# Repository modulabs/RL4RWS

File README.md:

# 모두의 연구소 : RL4RWS (시즌3)

## 연구실 소개
RL4RWS 랩은 **임베디드와 강화학습을 접목**하여 실제 환경에서 작동하는 다양한 모델을 직접 구현해 보는것을 목표로 합니다. 
 
## 연구실 목표
임베디드 분야와 강화학습 분야로 나누어서 세미나 진행 합니다.  

시즌 3의 진행 목표는 `NVIDIA Jetson TX2 기반 자율주행 RC카`를 제작하는 것입니다. 이를 위해 강화학습 이론과 RC카 제작 및 제어에 필요한 이론들을 학습할 계획입니다.   

### 강화학습 및 딥러닝 세미나 
#### 강화학습

김성훈 교수 강좌를 기반으로 강화학습 기초 세미나를 진행하였습니다.  
[모두를 위한 RL 강좌 유투브 채널](https://www.youtube.com/watch?v=dZ4vw6v3LcA&list=PLlMkM4tgfjnKsCWav-Z2F-MMFRx-2gMGG)  
[모두를 위한 머신러닝/딥러닝 강의 페이지](https://hunkim.github.io/ml/)  

#### 딥러닝
RL4RWS 연구원들의 실제 구현 사례를 바탕으로 세미나를 진행하였습니다.  
1. 조아라 연구원 : Udacity Self-Driving Car Nano-Degree 프로젝트 경험 공유  
    - [Traffic Sign Classifier](https://github.com/ahracho/CarND-Traffic-Sign-Classifier-Project)
    - [자율주행 시뮬레이션](https://github.com/ahracho/CarND-Behavioral-Cloning-P3) 
    - [Object Detection](https://github.com/ahracho/CarND-Vehicle-Detection)

2. 황보찬 연구원 : Yolo v3를 이용한 얼굴검출 및 표정인식  
3. 김민규 연구원 : GoogleNet 이용한 시각장애인용 길안내 (물체인식 프로젝트)   

### 임베디드 플랫폼 구축 관련 세미나
**1. NVIDIA Jetson TX2 (조진제 연구원)**   
    - Jetpack 설치 안내  
    - Jetson-inference 구조에 대한 설명과 데모  
    - Deep Learning deployment with tensorRT  

**2. TF-Slim 분석** : 저수준의 텐서플로우 API를 간편하게 사용할 수 있는 고수준 경량 API  
    **<참고자료>**  
    - [TF-slim 시작하기](https://www.popit.kr/tf-slim-%EC%8B%9C%EC%9E%91%ED%95%98%EA%B8%B0/)  
    - [TF-slim 분석 자료](./tf_slim)  
    - [TF-slim 예제 소스코드 (1) MNIST](https://github.com/socurites/tf-slim-tutorial)  
    - [TF-slim 예제 소스코드 (2) Dog Breed Classifier](https://github.com/socurites/dog-breed-classification.tf)  

**3. Tensorflow 활용한 YOLO**  
   **<참고자료>**  
    - [소스코드](./tf_yolo)  

### 센서 및 제어이론 관련 세미나
1. ROS 간단한 예제 설명 및 SLAM (이승진 연구원)  
2. PID 개론 (유지원 연구원)  
3. 최신 카메라 센서 동향 (장해강 연구원)  

### 참고자료
- [YOLOv2 On Jetson TX2](https://jkjung-avt.github.io/yolov2/)
- [YOLOv3 On Jetson TX2](https://jkjung-avt.github.io/yolov3/)
- [Jetson Race Car 예제](https://www.jetsonhacks.com/2016/01/26/jetson-racecar-part-3-esc-motor-control/)
- [버클리 강화학습 기반 RC카 github](https://github.com/gkahn13/gcg)  
- [TF-Slim](https://www.popit.kr/tf-slim-%EC%8B%9C%EC%9E%91%ED%95%98%EA%B8%B0/)
- [NVIDIA Jetson TX2 - JetPack](https://developer.nvidia.com/embedded/jetpack)  
- [모두를 위한 머신러닝/딥러닝](https://hunkim.github.io/ml/)

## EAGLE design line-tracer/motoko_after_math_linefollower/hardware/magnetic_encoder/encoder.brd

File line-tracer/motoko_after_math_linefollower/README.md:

# motoko_after_math_linefollower

본 프로젝트의 소스코드는 https://github.com/michalnand/motoko_after_math_linefollower 를 기반으로  
RL4RWS Lab에서 실습 상황에 맞게 수정하였습니다.

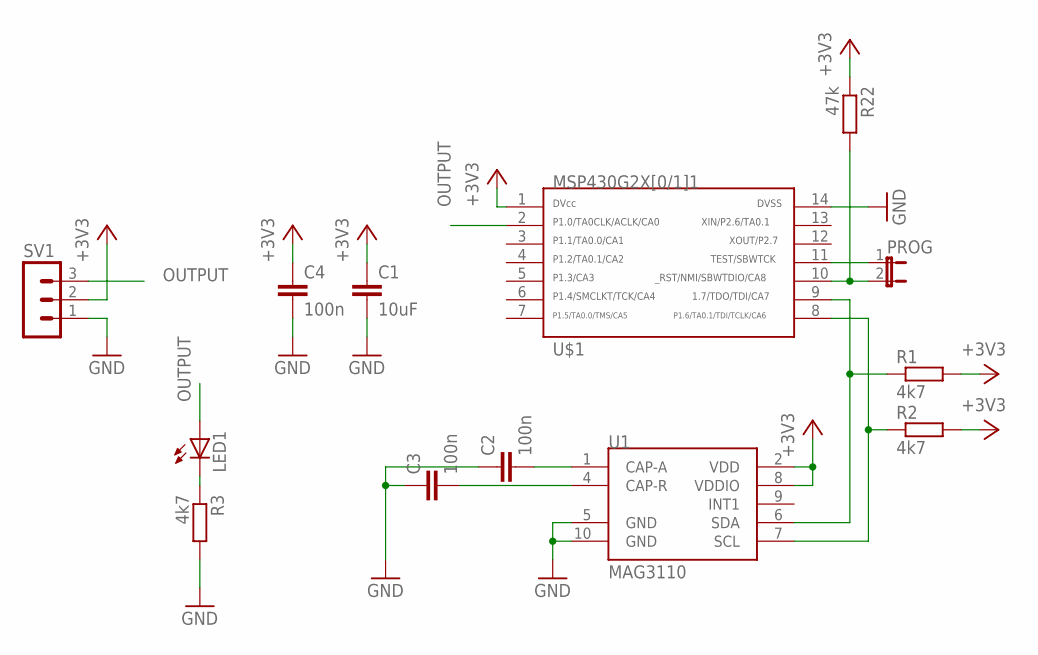
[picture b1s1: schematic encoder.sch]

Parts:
C1: 10uF; C0805
C2, C3, C4: 100n; C0805
LED1: LEDSML1206; SML1206
PROG: JP1E; JP1
R1, R2, R3: 4k7; M0805
R22: 47k; M0805
SV1: MA03-1
U1: MAG3110; DFN-10
U$1: G2X[0/1]1---PW14; PW14

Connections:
+3V3: C1.1, C4.1, R1.2, R2.2, R22.1, SV1.2, U1.2 (VDD), U1.8 (VDDIO), U$1.1
GND: C1.2, C2.1, C3.1, C4.2, R3.2, SV1.1, U1.5 (GND), U1.10 (GND), U$1.14
unnamed: PROG.1, U$1.11
unnamed: PROG.2, R22.2, U$1.10
unnamed: R1.1, U1.6 (SDA), U$1.9
unnamed: R2.1, U1.7 (SCL), U$1.8
unnamed: C3.2, U1.4 (CAP-R)
unnamed: C2.2, U1.1 (CAP-A)
unnamed: LED1.C, R3.1
OUTPUT: LED1.A, SV1.3, U$1.2

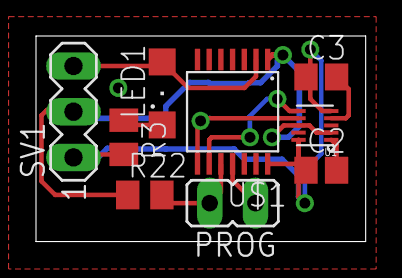
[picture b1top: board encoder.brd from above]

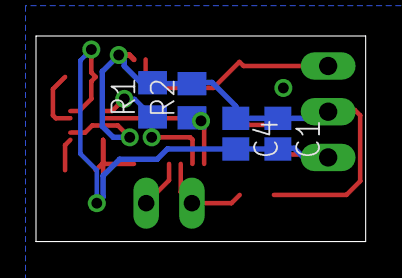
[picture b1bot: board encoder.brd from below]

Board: 2 copper layers, 18.3 x 11.4 mm, 13 parts (4 on the bottom side), 10 nets.

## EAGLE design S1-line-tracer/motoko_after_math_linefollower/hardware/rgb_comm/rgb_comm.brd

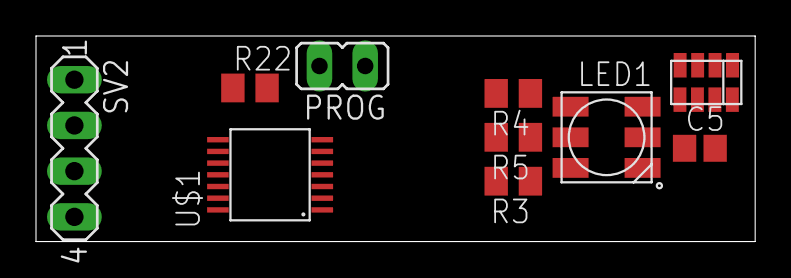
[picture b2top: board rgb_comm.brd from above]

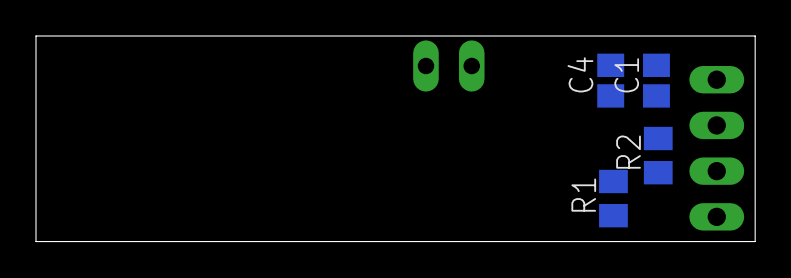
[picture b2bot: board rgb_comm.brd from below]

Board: 2 copper layers, 40.0 x 11.4 mm, 14 parts (4 on the bottom side), 13 nets, no tracks yet.

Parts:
C1, C5: 10uF; C0805
C4: 100n; C0805
LED1: ADAFRUIT_RGBLED5050
PROG: JP1
R1, R2: 4k7; M0805
R3, R4, R5: 330; M0805
R22: 47k; M0805
SV2: MA04-1
U$1: G2X[0/1]1---PW14; PW14
U$2: APDS9950

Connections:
+3V3: C1.1, C4.1, C5.1, R1.2, R2.2, R22.1, SV2.2, U$1.1, U$2.P$5, U$2.P$8
GND: C1.2, C4.2, C5.2, LED1.4, LED1.5, LED1.6, SV2.1, U$1.14, U$2.P$6
unnamed: PROG.1, U$1.11
unnamed: PROG.2, R22.2, U$1.10
unnamed: LED1.3, R3.1
unnamed: LED1.1, R4.1
unnamed: U$2.P$3, U$2.P$4
unnamed: LED1.2, R5.1
unnamed: R3.2, U$1.2
unnamed: R4.2, U$1.3
unnamed: R5.2, U$1.4
SCL: R2.1, SV2.3, U$1.8, U$2.P$7
SDA: R1.1, SV2.4, U$1.9, U$2.P$1

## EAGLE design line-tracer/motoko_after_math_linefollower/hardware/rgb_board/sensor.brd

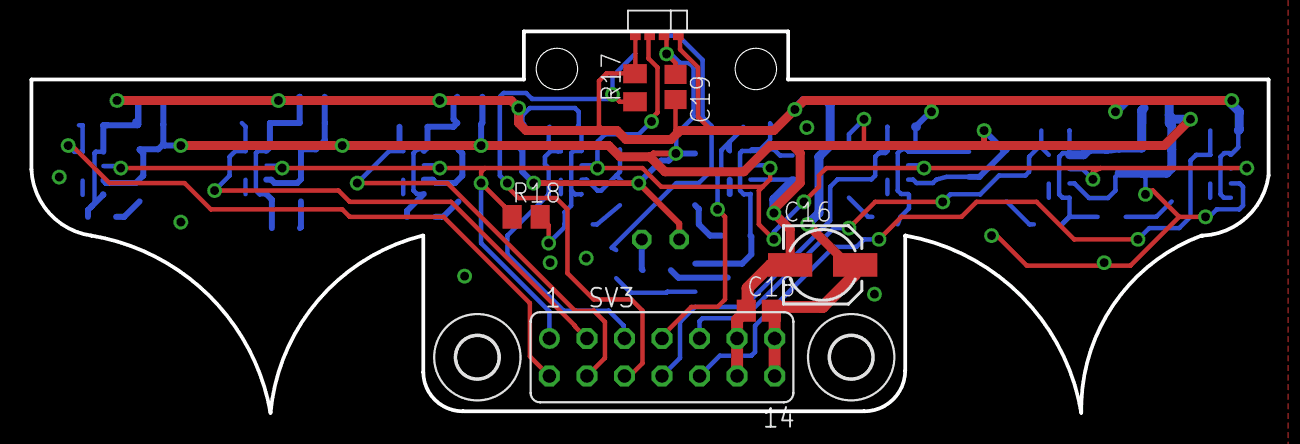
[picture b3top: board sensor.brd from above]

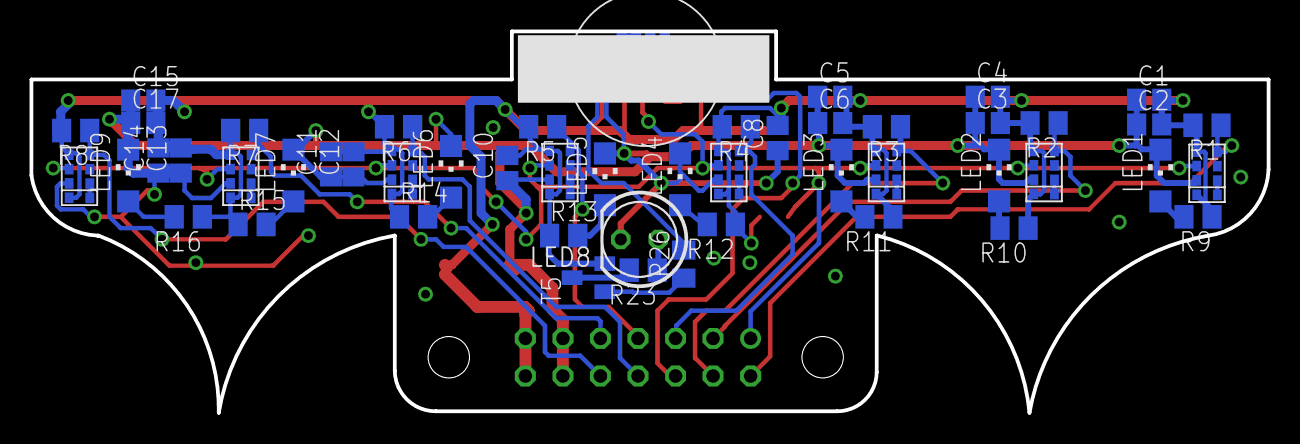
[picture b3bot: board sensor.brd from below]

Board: 2 copper layers, 83.7 x 25.8 mm, 60 parts (51 on the bottom side), 32 nets.

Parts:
C1, C3, C5, C11, C13, C15, C18: 10uF; C0805
C2, C4, C6, C8, C10, C12, C14, C17, C19: 100n; C0805
C16: 22uF; 153CLV-0505
H3, H4: MOUNT-HOLE2.8; 2,8
LED1, LED2, LED3, LED4, LED5, LED6, LED7, LED9: CHIPLED_1206
LED8: LED5MM
R1, R2, R3, R4, R5, R6, R7, R8, R17, R18: 4k7; M0805
R9, R10, R11, R12, R13, R14, R15, R16, R26: 330; M0805
R23: 22; M0805
SV3: FE07-2
T5: SOT23-BEC
U$1, U$4, U$5, U$6, U$7, U$8, U$9, U$10: APDS9950
U$2: APDS9950_EDGE
U$3: BALL_3/8

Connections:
+3V3: C1.2, C2.2, C3.2, C4.2, C5.2, C6.2, C8.2, C10.2, C11.2, C12.2, C13.2, C14.2, C15.2, C16.+, C17.2, C18.2, C19.2, R1.2, R2.2, R3.2, R4.2, R5.2, R6.2, R7.2, R8.2, R9.1, R10.1, R11.1, R12.1, R13.1, R14.1, R15.1, R16.1, R17.2, R18.2, SV3.13, SV3.14, T5.E, U$1.P$5, U$1.P$8, U$2.P$5, U$2.P$8, U$4.P$5, U$4.P$8, U$5.P$5, U$5.P$8, U$6.P$5, U$6.P$8, U$7.P$5, U$7.P$8, U$8.P$5, U$8.P$8, U$9.P$5, U$9.P$8, U$10.P$5, U$10.P$8
ADC0_: R8.1, SV3.10, U$10.P$1
ADC1_: R7.1, SV3.9, U$9.P$1
ADC2_: R6.1, SV3.8, U$8.P$1
ADC3_: R5.1, SV3.7, U$7.P$1
ADC4_: R4.1, SV3.5, U$6.P$1
ADC5_: R3.1, SV3.4, U$5.P$1
ADC6_: R2.1, SV3.3, U$4.P$1
ADC7_: R1.1, SV3.2, U$1.P$1
ADC8_: R17.1, SV3.6, U$2.P$1
GND: C1.1, C2.1, C3.1, C4.1, C5.1, C6.1, C8.1, C10.1, C11.1, C12.1, C13.1, C14.1, C15.1, C16.-, C17.1, C18.1, C19.1, LED1.C, LED2.C, LED3.C, LED4.C, LED5.C, LED6.C, LED7.C, LED8.K, LED9.C, SV3.11, SV3.12, U$1.P$6, U$2.P$6, U$4.P$6, U$5.P$6, U$6.P$6, U$7.P$6, U$8.P$6, U$9.P$6, U$10.P$6
unnamed: R23.2, T5.C
unnamed: U$4.P$3, U$4.P$4
unnamed: LED1.A, R9.2
unnamed: U$1.P$3, U$1.P$4
unnamed: LED2.A, R10.2
unnamed: LED3.A, R11.2
unnamed: LED4.A, R12.2
unnamed: LED5.A, R13.2
unnamed: U$5.P$3, U$5.P$4
unnamed: LED6.A, R14.2
unnamed: LED7.A, R15.2
unnamed: U$6.P$3, U$6.P$4
unnamed: LED9.A, R16.2
unnamed: R26.2, U$2.P$3, U$2.P$4
unnamed: U$7.P$3, U$7.P$4
unnamed: U$8.P$3, U$8.P$4
unnamed: U$9.P$3, U$9.P$4
unnamed: LED8.A, R23.1
unnamed: U$10.P$3, U$10.P$4
unnamed: R26.1, T5.B
SCL: R18.1, SV3.1, U$1.P$7, U$2.P$7, U$4.P$7, U$5.P$7, U$6.P$7, U$7.P$7, U$8.P$7, U$9.P$7, U$10.P$7

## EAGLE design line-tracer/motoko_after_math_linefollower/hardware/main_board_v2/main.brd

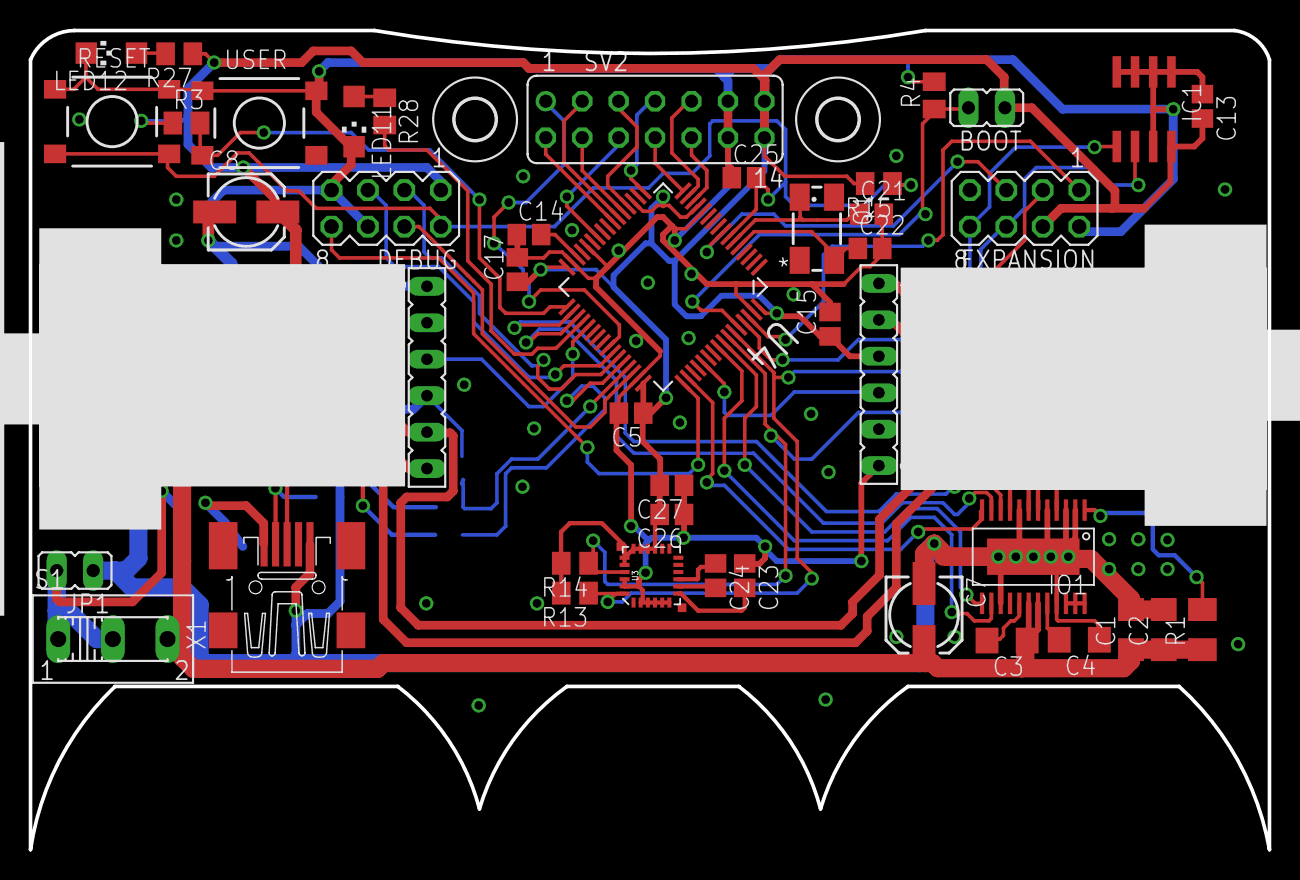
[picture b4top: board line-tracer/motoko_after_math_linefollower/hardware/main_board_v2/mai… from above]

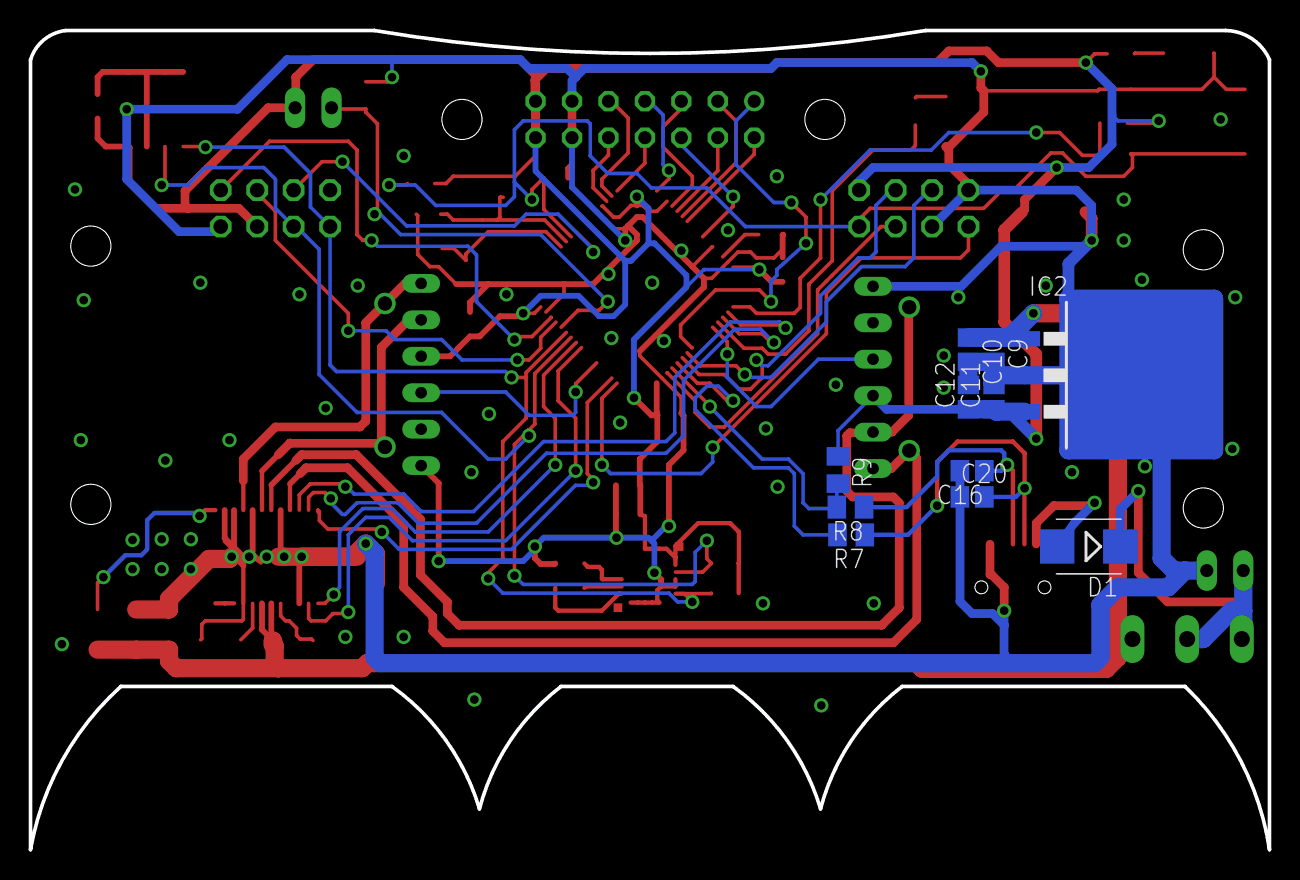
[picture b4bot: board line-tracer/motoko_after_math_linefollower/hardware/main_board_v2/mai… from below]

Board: 2 copper layers, 86.4 x 57.1 mm, 59 parts (11 on the bottom side), 55 nets.

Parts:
BOOT: JP1
C1: 100n; C1206
C2: 10uF; C1206
C3: 10n; C1206
C4: 1uF; C1206
C5, C9, C11, C13, C15, C17, C25, C26: 100n; C0805
C7, C8: 22uF; 153CLV-0505
C10, C12, C27: 10uF; C0805
C14, C23: 4.7uF; C0805
C16, C20: 22p; C0805
C21, C22: 18p; C0805
C24: 220n; C0805
D1: SMB
DEBUG: MA04-2
EXPANSION: MA04-2
H1, H2: MOUNT-HOLE2.8; 2,8
IC1: 24AA32ASN; SO-08
IC2: LM2937; TO263-3
IO1: DRV8834; DRV8834_PCK
JP1: 2 CellLi-Pol; JP1
LED11: CHIPLED_1206
LED12: poweron; CHIPLED_1206
Q1: 8MHz; CTS406
R1: 47k; M1206
R3, R4, R15: 47k; M0805
R7, R8: 22; M0805
R9: 1k5; M0805
R13, R14: 4k7; M0805
R27, R28: 330; M0805
RESET: DTSM-6
S1: 255SB
SV1, SV3: FE06
SV2: FE07-2
U3: LSM9DS0; LGA-24
U4: STM32F303RCT6; QFP50P1200X1200X160-64N
U$1, U$2: MICRO_METAL_GEAR_MOTOR
USER: DTSM-6
X1: MINI-USB-32005-201; 32005-201

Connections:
+3V3: BOOT.1, C5.1, C8.+, C11.1, C12.1, C13.2, C15.1, C17.1, C26.2, C27.2, DEBUG.1, EXPANSION.4, IC1.8, IC2.3, R3.1, R9.1, R13.2, R14.2, R15.2, R27.1, SV1.3, SV2.13, SV2.14, SV3.3, U3.15, U3.16, U3.17, U3.18, U3.19, U3.20, U4.13, U4.19, U4.32, U4.48, U4.64
ADC0: SV2.10, U4.14
ADC1: SV2.9, U4.15
ADC2: SV2.8, U4.16
ADC3: SV2.7, U4.17
ADC4: SV2.5, U4.20
ADC5: SV2.4, U4.21
ADC6: SV2.3, U4.22
ADC7: SV2.2, U4.23
ADC8: SV2.6, U4.26
AENBL: IO1.10, U4.34
APHASE: IO1.13, U4.57
BATT: D1.C, JP1.2, S1.1, S1.2
BENBL: IO1.11, U4.35
BOOT: BOOT.2, R4.1, U4.60
BPHASE: IO1.12, U4.50
CAM_AO: EXPANSION.5, U4.8
CAM_CLK: EXPANSION.3, U4.61
CAM_SI: EXPANSION.1, U4.62
GND: C1.2, C2.2, C4.1, C5.2, C7.-, C8.-, C9.2, C10.2, C11.2, C12.2, C13.1, C14.1, C15.2, C16.2, C17.2, C20.1, C21.2, C22.2, C23.1, C25.1, C26.1, C27.1, DEBUG.6, DEBUG.7, EXPANSION.2, IC1.1, IC1.2, IC1.3, IC1.4, IC1.7, IC2.2, IO1.2, IO1.3, IO1.5, IO1.8, IO1.15, IO1.21, IO1.PAD, JP1.1, LED11.C, LED12.C, R4.2, RESET.1, RESET.2, SV1.6, SV2.11, SV2.12, SV3.6, U3.2, U3.3, U3.4, U3.5, U3.6, U3.22, U3.23, U4.12, U4.28, U4.31, U4.47, U4.63, USER.1, USER.2, X1.5
IR_CONTROLL: SV2.1, U4.41
LED_1: R28.2, U4.36
LEFT_ENC: SV1.4, U4.37
M1: IO1.14, U4.56
unnamed: IO1.4, SV3.1, U$1.P$1
unnamed: IO1.6, SV3.2, U$1.P$2
unnamed: IO1.9, SV1.1, U$2.P$1
unnamed: IO1.7, SV1.2, U$2.P$2
unnamed: C3.2, IO1.17
unnamed: C23.2, U3.7
unnamed: C24.2, U3.8
unnamed: IO1.22, IO1.23, IO1.24
unnamed: IO1.1, R1.2
unnamed: C24.1, U3.9
unnamed: C14.2, U4.30
unnamed: C4.2, IO1.20
unnamed: LED12.A, R27.2
unnamed: LED11.A, R28.1
unnamed: C20.2, R7.1, X1.2
unnamed: C16.1, R8.1, X1.3
unnamed: D1.A, X1.1
OSCIN: C22.1, Q1.3, U4.5
OSCOUT: C21.1, Q1.1, U4.6
RESET: C25.2, DEBUG.2, R15.1, RESET.3, RESET.4, U4.7
RIGHT_ENC: SV3.4, U4.53
SCL: EXPANSION.6, IC1.6, R14.1, U3.21, U4.58
SDA: EXPANSION.8, IC1.5, R13.1, U3.24, U4.59
SWCLK: DEBUG.8, U4.49
SWDIO: DEBUG.4, U4.46
UART_RX: DEBUG.3, U4.43
UART_TX: DEBUG.5, U4.42
USBDM: R7.2, U4.44
USBDP: R8.2, R9.2, U4.45
USER_KEY_1: R3.2, U4.33, USER.3
VCC: C1.1, C2.1, C3.1, C7.+, C9.1, C10.1, IC2.1, IO1.18, IO1.19, R1.1, S1.3

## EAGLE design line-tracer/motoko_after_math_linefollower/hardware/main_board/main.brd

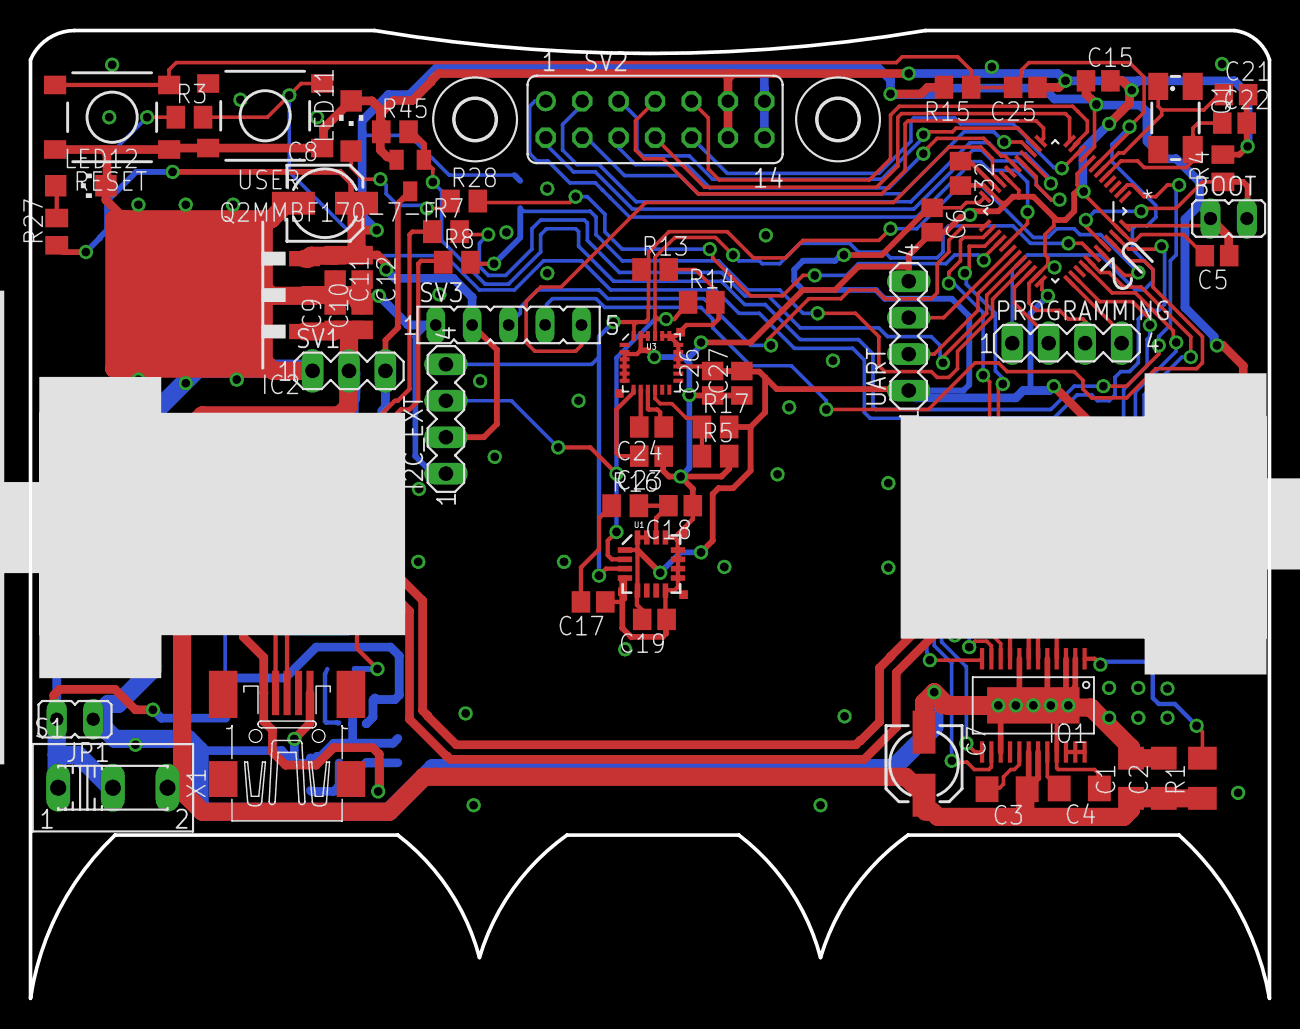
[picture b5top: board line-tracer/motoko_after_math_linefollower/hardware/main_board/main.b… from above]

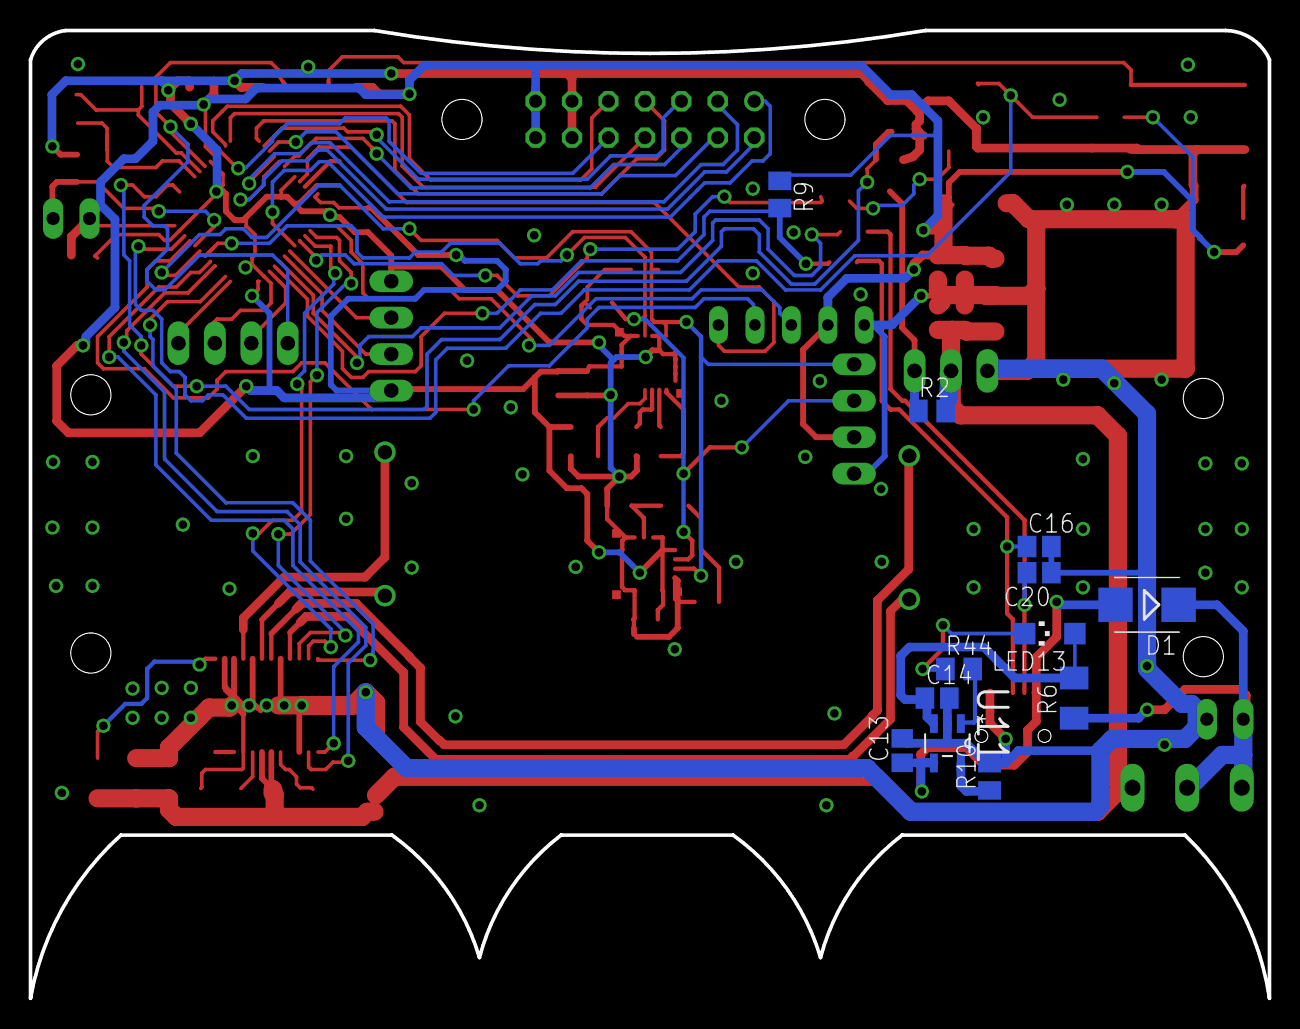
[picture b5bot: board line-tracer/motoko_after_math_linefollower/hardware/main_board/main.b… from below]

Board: 2 copper layers, 86.4 x 67.5 mm, 75 parts (12 on the bottom side), 62 nets.

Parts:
BOOT: JP1
C1: 100n; C1206
C2: 10uF; C1206
C3: 10n; C1206
C4: 1uF; C1206
C5, C9, C11, C15, C19, C25, C26: 100n; C0805
C6, C10, C12, C13, C14, C27: 10uF; C0805
C7, C8: 22uF; 153CLV-0505
C16, C20: 22p; C0805
C17: 470n; C0805
C18: 10n; C0805
C21, C22: 18p; C0805
C23, C32: 4.7uF; C0805
C24: 220n; C0805
D1: SMB
H1, H2: MOUNT-HOLE2.8; 2,8
I2C_EXT: MA04-1
IC2: LM2937; TO263-3
IO1: DRV8834; DRV8834_PCK
JP1: 2 CellLi-Pol; JP1
LED11: CHIPLED_1206
LED12: poweron; CHIPLED_1206
LED13: charging; CHIPLED_1206
PROGRAMMING: MA04-1
Q1: 8MHz; CTS406
Q2MMBF170-7-F: BSS123; SOT23
R1: 47k; M1206
R2, R3, R4, R5, R15, R17, R45: 47k; M0805
R6: 0R USE ONLY FOR SINGLE CELL; M1206
R7, R8: 22; M0805
R9: 1k5; M0805
R10, R16: 10k; M0805
R13, R14: 4k7; M0805
R27, R28, R44: 330; M0805
RESET: DTSM-6
S1: 255SB
SV1: SERVO/PWM; MA03-1
SV2: FE07-2
SV3: TSL1401 CAMERA; FE05-1
U1: L3G4200D; LGA16-4X4
U2: STM32F103C6T6A; QFP50P900X900X160-48N
U3: LSM9DS0; LGA-24
U11: MCP73831T-2DCI/OT; SOT95P270X145-5N
U$1, U$2: MICRO_METAL_GEAR_MOTOR
UART: MA04-1
USER: DTSM-6
X1: MINI-USB-32005-201; 32005-201

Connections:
+3V3: BOOT.1, C5.1, C6.1, C8.+, C11.1, C12.1, C15.1, C19.2, C26.2, C27.2, I2C_EXT.2, IC2.3, R3.1, R9.1, R13.2, R14.2, R15.2, R17.2, R27.1, SV2.13, SV2.14, SV3.2, U1.1, U1.5, U1.15, U1.16, U2.9, U2.24, U2.36, U2.48, U3.15, U3.16, U3.17, U3.18, U3.19, U3.20, UART.1
ADC0: SV2.10, U2.10
ADC1: SV2.9, U2.11
ADC2: SV2.8, U2.12
ADC3: SV2.7, U2.13
ADC4: SV2.5, U2.14
ADC5: SV2.4, U2.15
ADC6: SV2.3, U2.16
ADC7: SV2.2, U2.17
ADC8: SV2.6, U2.18
AENBL: IO1.10, U2.26
APHASE: IO1.13, U2.41
BATT: D1.C, JP1.2, R6.1, S1.1, S1.2
BENBL: IO1.11, U2.27
BPHASE: IO1.12, U2.38
CAM_AO: SV3.3, U2.25
CAM_CLK: SV3.4, U2.45
CAM_SI: SV3.5, U2.21
GND: C1.2, C2.2, C4.1, C5.2, C6.2, C7.-, C8.-, C9.2, C10.2, C11.2, C12.2, C13.2, C14.2, C15.2, C16.2, C17.1, C18.1, C19.1, C20.1, C21.2, C22.2, C23.1, C25.1, C26.1, C27.1, C32.2, I2C_EXT.1, IC2.2, IO1.2, IO1.3, IO1.5, IO1.8, IO1.15, IO1.21, IO1.PAD, JP1.1, LED11.C, LED12.C, PROGRAMMING.3, Q2MMBF170-7-F.2, R4.2, R5.2, R10.2, R45.1, RESET.1, RESET.2, SV1.1, SV2.11, SV2.12, SV3.1, U1.4, U1.8, U1.9, U1.10, U1.11, U1.12, U1.13, U2.8, U2.20, U2.23, U2.35, U2.47, U3.2, U3.3, U3.4, U3.5, U3.6, U3.22, U3.23, U11.2, UART.4, USER.1, USER.2, X1.5
IR_CONTROLL: SV2.1, U2.29
LED_1: R28.2, U2.28
M1: IO1.14, U2.40
unnamed: IO1.4, U$1.P$1
unnamed: IO1.6, U$1.P$2
unnamed: IO1.9, U$2.P$1
unnamed: IO1.7, U$2.P$2
unnamed: C3.2, IO1.17
unnamed: C23.2, U3.7
unnamed: C24.2, U3.8
unnamed: IO1.22, IO1.23, IO1.24
unnamed: IO1.1, R1.2
unnamed: C24.1, U3.9
unnamed: C32.1, U2.22
unnamed: BOOT.2, R4.1, U2.44
unnamed: R44.2, U11.1
unnamed: R5.1, R17.1, U3.10
unnamed: C18.2, R16.2, U1.14
unnamed: C17.2, R16.1
unnamed: C4.2, IO1.20
unnamed: LED12.A, R27.2
unnamed: LED13.C, R44.1
unnamed: Q2MMBF170-7-F.3, R2.1, SV1.3
unnamed: LED11.A, R28.1
unnamed: C14.1, LED13.A, R6.2, U11.3
unnamed: R10.1, U11.5
unnamed: C20.2, R7.1, X1.2
unnamed: C16.1, R8.1, X1.3
unnamed: C13.1, D1.A, U11.4, X1.1
OSCIN: C22.1, Q1.3, U2.5
OSCOUT: C21.1, Q1.1, U2.6
RESET: C25.2, PROGRAMMING.1, R15.1, RESET.3, RESET.4, U2.7
SCL: I2C_EXT.3, R14.1, U1.2, U2.42, U3.21
SDA: I2C_EXT.4, R13.1, U1.3, U2.43, U3.24
SERVO: Q2MMBF170-7-F.1, R45.2, U2.2
SWCLK: PROGRAMMING.4, U2.37
SWDIO: PROGRAMMING.2, U2.34
UART_RX: U2.31, UART.2
UART_TX: U2.30, UART.3
USBDM: R7.2, U2.32
USBDP: R8.2, R9.2, U2.33
USER_KEY_1: R3.2, U2.46, USER.3
VCC: C1.1, C2.1, C3.1, C7.+, C9.1, C10.1, IC2.1, IO1.18, IO1.19, R1.1, R2.2, S1.3, SV1.2

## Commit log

2017-11-13 Edit Readme file : Add description of RL4RWS lab
    [Changed by] ah-ra.cho
2017-11-13 Make folder for RL and embeded seminar for each
    [Changed by] ah-ra.cho
2017-11-14 Update github guide
    [Changed by] ah-ra.cho
2017-11-19 Upload motoko_linefollower code - Revised for stm32f103 version - UART initialization code added
    [Changed by] ah-ra.cho
2017-11-19 Add Q-Learning examples - Dummy Q-learning - Exploit & Exploration + Discounted Reward - Non-deterministic Environment
    [Changed by] ah-ra.cho
2017-11-20 Add Q-Network examples
    [Changed by] ah-ra.cho
2018-01-22 Add new folder for autonomous self-learning system
    [Changed by] ah-ra.cho
2018-02-04 Add Submodule for project
2018-02-16 [Arduino] Update Arduino examples used in Seminar
    [Changed by] ah-ra.cho
2018-02-20 [Fritzing] Upload Ultrasound example
    [Changed by] ah-ra.cho
2018-04-10 [Project] Autonomous car project based on Q-Learning - Based code for Q-learning
    [Changed by] ah-ra.cho
2018-04-12 [Update] update in autonomous car C based code - data struct added - discretization/get_reward function implemented
    [Changed by] ah-ra.cho
2018-08-28 [RL4RWS 시즌3] 세미나 진행 사항 업데이트 - TF-Slim 실습 예제 추가 - YOLO w/ TF 예제 추가 (data 제외) - README 변경
    [Type] Normal / Bug Fix / Implementation
    [Changed by] ah-ra.cho
2018-10-27 폴더 구조 변경 - 시즌별로 폴더 구성
2018-10-27 시즌3 자율주행차 - 참고자료 : 서브모듈 추가 (Alpha Car) - Modu Car(랩에서 작업한 RC카) 코드 추가
2018-10-30 아두이노 초음파센서 실습 자료 업로드 - Fritzing (모터 + 초음파센서 5개 + BT센서) - 아두이노 코드 (초음파 1개 연결)

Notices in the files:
parts and their libraries:
SparkFun-Sensors: Licensing: Creative Commons ShareAlike 4.0 International - https://creativecommons.org/licenses/by-sa/4.0
